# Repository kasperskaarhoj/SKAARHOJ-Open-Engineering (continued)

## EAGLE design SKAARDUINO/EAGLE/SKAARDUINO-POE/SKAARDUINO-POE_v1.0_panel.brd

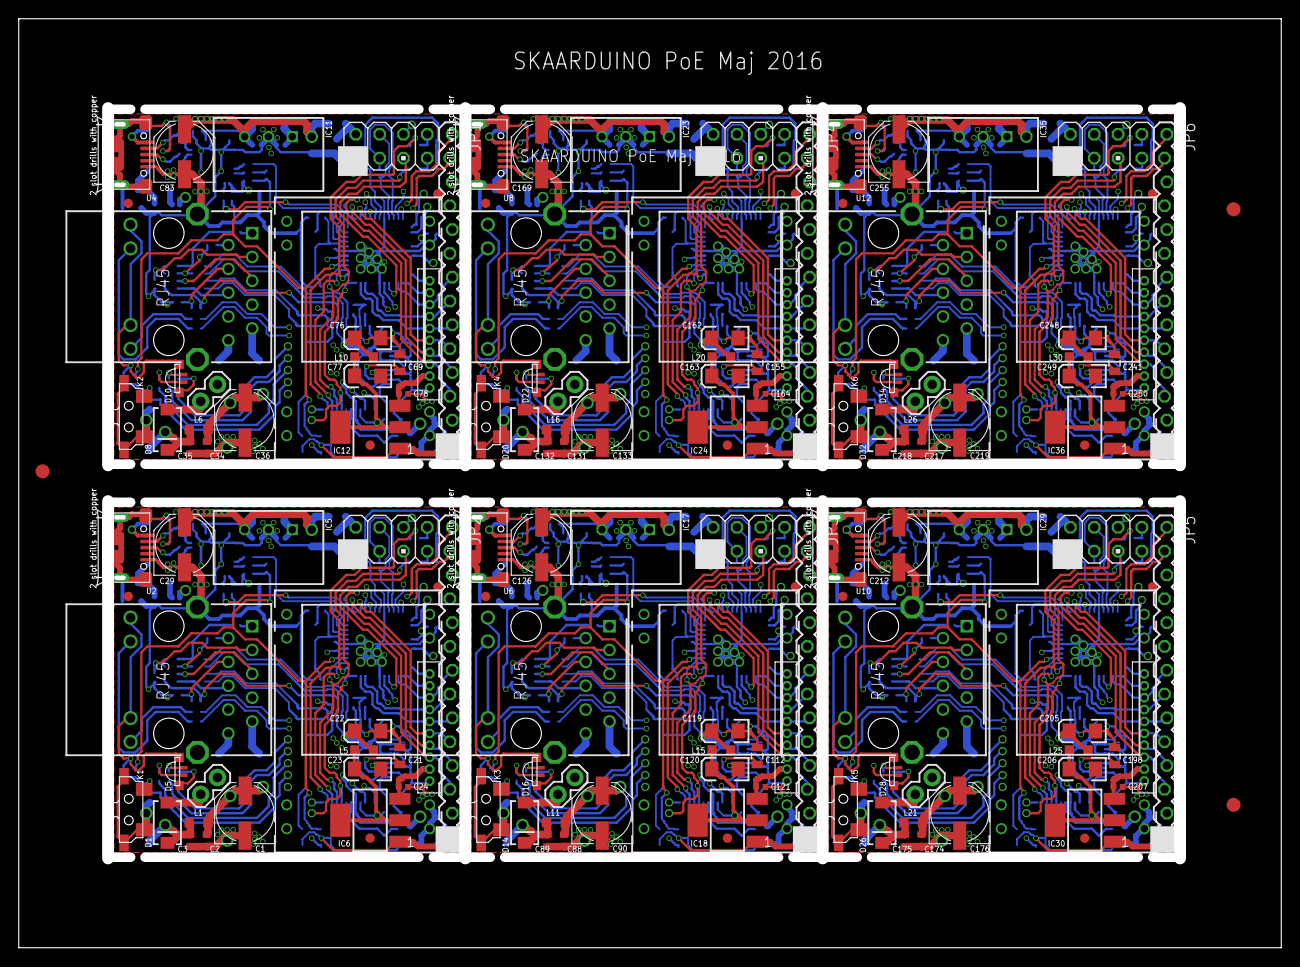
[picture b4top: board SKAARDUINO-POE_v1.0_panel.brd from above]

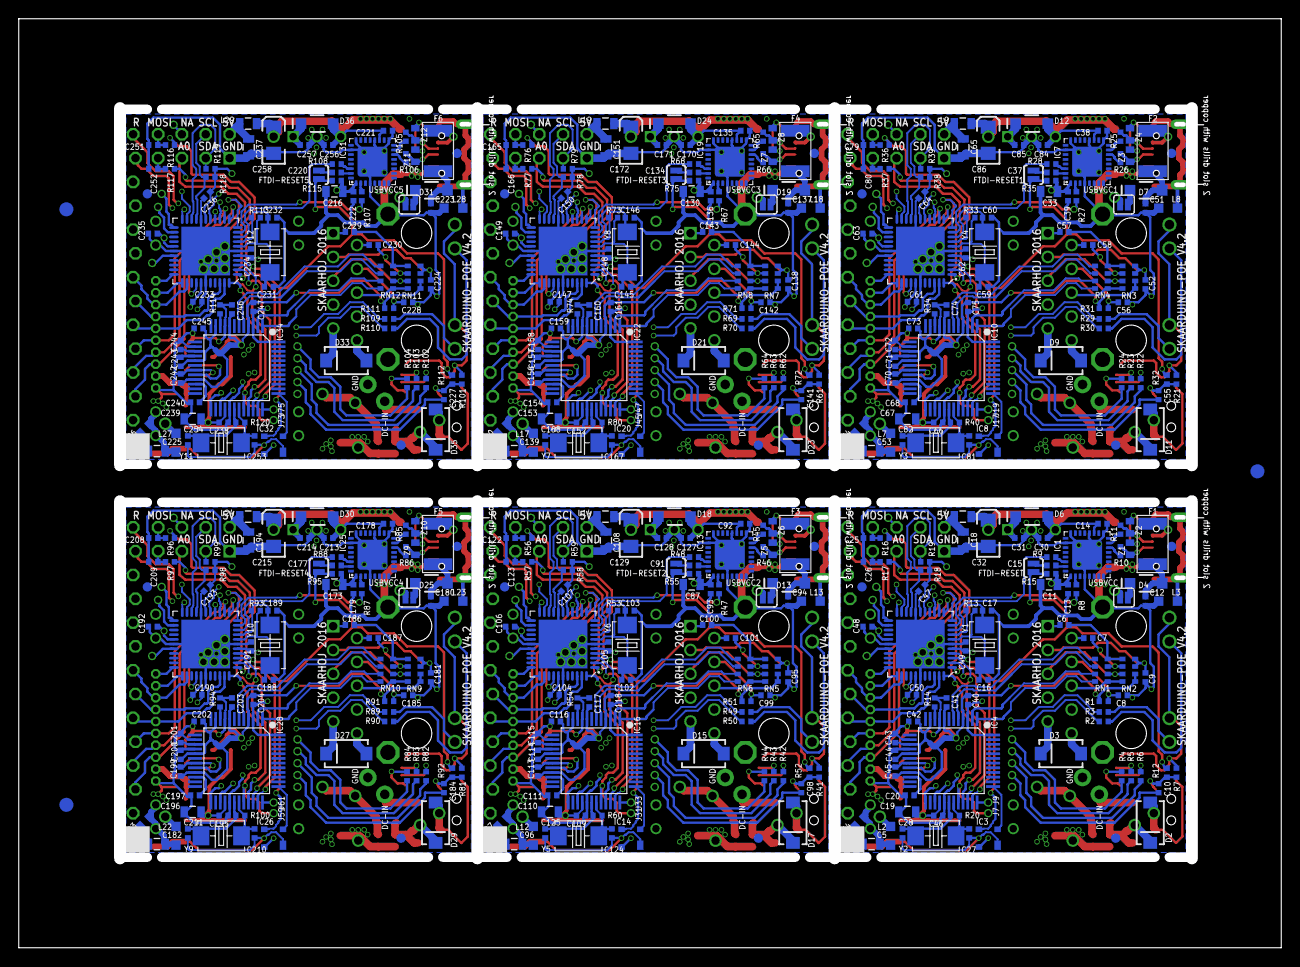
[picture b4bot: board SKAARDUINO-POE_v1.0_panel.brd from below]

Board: 4 copper layers, 134.6 x 99.1 mm, 690 parts (474 on the bottom side), 486 nets.

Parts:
C1, C36, C90, C133, C176, C219: 100uF/25V; PANASONIC_D
C2, C3, C4, C34, C35, C54, C88, C89, C97, C131, C132, C140, C174, C175, C183, C217, C218, C226: 100nF/25V; C0402
C5, C53, C96, C139, C182, C225: 10uF/25V; 0805
C6, C7, C57, C58, C100, C101, C143, C144, C186, C187, C229, C230: 6.8nF; 0402C
C8, C56, C99, C142, C185, C228: 22nF; 0402C
C9, C20, C52, C68, C95, C111, C138, C154, C181, C197, C224, C240: 10nF; 0402C
C10, C12, C51, C55, C94, C98, C137, C141, C180, C184, C223, C227: 1uF; 0402C
C11, C33, C87, C130, C173, C216: 22uF; 0805
C13, C14, C15, C24, C30, C37, C38, C39, C40, C41, C42, C43, C44, C45, C46, C47, C48, C49, C50, C61, C62, C63, C64, C66, C70, C71, C72, C73, C74, C75, C78, C84, C91, C92, C93, C104, C105, C106, C107, C109, C113, C114, C115, C116, C117, C118, C121, C127, C134, C135, C136, C147, C148, C149, C150, C152, C156, C157, C158, C159, C160, C161, C164, C170, C177, C178, C179, C190, C191, C192, C193, C195, C199, C200, C201, C202, C203, C204, C207, C213, C220, C221, C222, C233, C234, C235, C236, C238, C242, C243, C244, C245, C246, C247, C250, C256: 100nF; 0402C
C16, C17, C25, C26, C59, C60, C79, C80, C102, C103, C122, C123, C145, C146, C165, C166, C188, C189, C208, C209, C231, C232, C251, C252: 22pF; 0402C
C18, C65, C108, C151, C194, C237: 22uF/6.3V; 0805
C19, C67, C110, C153, C196, C239: 10uF/16V; 0805
C21, C69, C112, C155, C198, C241: 4.7uF; 0805
C22, C23, C32, C76, C77, C86, C119, C120, C129, C162, C163, C172, C205, C206, C215, C248, C249, C258: 10uF 6.3V A TANT; EIA3216
C27, C28, C81, C82, C124, C125, C167, C168, C210, C211, C253, C254: 18pF; 0402C
C29, C83, C126, C169, C212, C255: 330uF/6.3V; PANASONIC_D
C31, C85, C128, C171, C214, C257: 100nF/25V; 0402C
D1, D8, D14, D20, D26, D32: MBRA210LT3G; SMA-DIODE
D2, D3, D9, D11, D15, D17, D21, D23, D27, D29, D33, D35: SMAJ58CA; SMA-DIODE
D4, D6, D7, D12, D13, D18, D19, D24, D25, D30, D31, D36: MBR0520; SOD-123
D5, D10, D16, D22, D28, D34: KPFA-3010RGBC-11; LED-TRICOLOR-SMD
E$1, E$2, E$3: FIDUCIAL-1.5X3
E$4, E$5, E$6: FIDUCIAL-1.5X3_BOTTOM
F1, F2, F3, F4, F5, F6: SMD-PPTC-500MA-15V(1812); F1812
FID1, FID2, FID3, FID4, FID5, FID6, FID7, FID8, FID9, FID10, FID11, FID12, FID13, FID14, FID15, FID16, FID17, FID18, FID19, FID20, FID21, FID22, FID23, FID24, FID25, FID26, FID27, FID28, FID29, FID30, FID31, FID32, FID33, FID34, FID35, FID36: FIDUCIAL1X2.5; FIDUCIAL-1X2.5
FTDI-RESET, FTDI-RESET1, FTDI-RESET2, FTDI-RESET3, FTDI-RESET4, FTDI-RESET5: SOLDERJUMPERNO; SJ_2S-NO
IC1, IC7, IC13, IC19, IC25, IC31: FT232RQ; QFN32
IC2, IC9, IC15, IC21, IC27, IC33: ATMEGA1284P; QFN-44M1
IC3, IC8, IC14, IC20, IC26, IC32: APX811-44UG-7; SOT143-R
IC4, IC10, IC16, IC22, IC28, IC34: WizNet W5500; LQFP-48
IC5, IC11, IC17, IC23, IC29, IC35: RECOM 785.0-1.0; RECOM_785.0-1.0
IC6, IC12, IC18, IC24, IC30, IC36: LD1117S33CTR; SOT-223
J1, J3, J4, J6, J7, J13, J14, J17, J23, J24, J25, J26, J27, J28, J31, J37, J38, J39, J40, J41, J42, J45, J51, J52, J53, J54, J55, J56, J59, J65, J66, J67, J68, J69, J70, J73, J79, J80, J81, J82, J83, J84: SS; M1X1
J2, J15, J29, J43, J57, J71: DC IN JACK; 1X02
J5, J16, J30, J44, J58, J72: M04X2M2X4SMALLER; M2X4SMALLER
J8, J18, J32, J46, J60, J74: M10_1.27; M10X1
J9, J19, J33, J47, J61, J75: W_INT; M1X1
J10, J20, J34, J48, J62, J76: D11; M1X1
J11, J21, J35, J49, J63, J77: D12; M1X1
J12, J22, J36, J50, J64, J78: AREF; M1X1
JP1, JP2, JP3, JP4, JP5, JP6: M14LOCK; 1X14_LOCK
K1, K2, K3, K4, K5, K6: RESET/CFG; SW4-SMD-7.0X3.5X3.5MM-90D
L1, L2, L3, L6, L7, L8, L11, L12, L13, L16, L17, L18, L21, L22, L23, L26, L27, L28: Bead ILHB0805ER121V; L2012C
L4, L9, L14, L19, L24, L29: Bead ILHB0805ER121V; 0805
L5, L10, L15, L20, L25, L30: 1uH 250mA 0805; L2012C
R1, R31, R51, R71, R91, R111: 10R/1%; 0402
R2, R3, R29, R30, R49, R50, R69, R70, R89, R90, R109, R110: 470R; 0402
R4, R24, R44, R64, R84, R104: 390R; 0402
R5, R23, R43, R63, R83, R103: 540R; 0402
R6, R22, R42, R62, R82, R102: 2K7; 0402
R7, R15, R21, R35, R41, R55, R61, R75, R81, R95, R101, R115: 10K; 0402
R8, R9, R27, R28, R47, R48, R67, R68, R87, R88, R107, R108: 1K; 0402
R10, R11, R25, R26, R45, R46, R65, R66, R85, R86, R105, R106: 22R; 0402
R12, R32, R52, R72, R92, R112: 100K; 0402
R13, R20, R33, R40, R53, R60, R73, R80, R93, R100, R113, R120: 1M; 0402
R14, R34, R54, R74, R94, R114: 12K4 / 1%; 0402
R16, R17, R36, R37, R56, R57, R76, R77, R96, R97, R116, R117: 100R; 0402
R18, R19, R38, R39, R58, R59, R78, R79, R98, R99, R118, R119: 1K5; 0402
RN1, RN4, RN6, RN8, RN10, RN12: 33R; CAY16
RN2, RN3, RN5, RN7, RN9, RN11: 49R9 1%; CAY16
U1, U3, U5, U7, U9, U11: HY931147C-RJ45; HY931147C
U2, U4, U6, U8, U10, U12: MICRO USB; MICRO-USB5+4P-SMD-0.65-B
U$1, U$2, U$3, U$4, U$5, U$7: AG9800PTH
USBVCC, USBVCC1, USBVCC2, USBVCC3, USBVCC4, USBVCC5: SOLDERJUMPERNC; SJ_2S
Y1, Y4, Y6, Y8, Y10, Y12: 20MhZ; X2-SMD-5.0X3.2X1.3MM
Y2, Y3, Y5, Y7, Y9, Y11: 25MhZ; X2-SMD-5.0X3.2X1.3MM
Z1, Z2, Z3, Z4, Z5, Z6, Z7, Z8, Z9, Z10, Z11, Z12: PGB1010603; C0402

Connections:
3V3A: C22.A, C40.1, C41.1, C42.1, C43.1, C44.1, C45.1, IC4.4, IC4.8, IC4.11, IC4.15, IC4.17, IC4.21, L5.2, R1.2, RN2.5, RN2.6
3V3A1: C70.1, C71.1, C72.1, C73.1, C74.1, C75.1, C76.A, IC10.4, IC10.8, IC10.11, IC10.15, IC10.17, IC10.21, L10.2, R31.2, RN3.5, RN3.6
3V3A2: C113.1, C114.1, C115.1, C116.1, C117.1, C118.1, C119.A, IC16.4, IC16.8, IC16.11, IC16.15, IC16.17, IC16.21, L15.2, R51.2, RN5.5, RN5.6
3V3A3: C156.1, C157.1, C158.1, C159.1, C160.1, C161.1, C162.A, IC22.4, IC22.8, IC22.11, IC22.15, IC22.17, IC22.21, L20.2, R71.2, RN7.5, RN7.6
3V3A4: C199.1, C200.1, C201.1, C202.1, C203.1, C204.1, C205.A, IC28.4, IC28.8, IC28.11, IC28.15, IC28.17, IC28.21, L25.2, R91.2, RN9.5, RN9.6
3V3A5: C242.1, C243.1, C244.1, C245.1, C246.1, C247.1, C248.A, IC34.4, IC34.8, IC34.11, IC34.15, IC34.17, IC34.21, L30.2, R111.2, RN11.5, RN11.6
3V3D: C19.1, C23.A, C46.1, IC4.28, IC6.2, IC6.TER, L5.1
3V3D1: C66.1, C67.1, C77.A, IC10.28, IC12.2, IC12.TER, L10.1
3V3D2: C109.1, C110.1, C120.A, IC16.28, IC18.2, IC18.TER, L15.1
3V3D3: C152.1, C153.1, C163.A, IC22.28, IC24.2, IC24.TER, L20.1
3V3D4: C195.1, C196.1, C206.A, IC28.28, IC30.2, IC30.TER, L25.1
3V3D5: C238.1, C239.1, C249.A, IC34.28, IC36.2, IC36.TER, L30.1
5V: C11.1, C13.2, C14.2, C24.1, C29.+, C30.1, C32.A, C47.1, C48.1, C49.1, C50.1, D5.A, D6.2, IC1.1, IC1.19, IC2.5, IC2.17, IC2.27, IC2.38, IC3.4, IC5.P$3, IC6.3, J8.2, JP2.13, L4.2, R7.2, R15.2, R18.2, R19.2, U1.P$11, U1.P$13, USBVCC.2
5V1: C33.1, C38.2, C39.2, C61.1, C62.1, C63.1, C64.1, C78.1, C83.+, C84.1, C86.A, D10.A, D12.2, IC7.1, IC7.19, IC8.4, IC9.5, IC9.17, IC9.27, IC9.38, IC11.P$3, IC12.3, J18.2, JP1.13, L9.2, R21.2, R35.2, R38.2, R39.2, U3.P$11, U3.P$13, USBVCC1.2
5V2: C87.1, C92.2, C93.2, C104.1, C105.1, C106.1, C107.1, C121.1, C126.+, C127.1, C129.A, D16.A, D18.2, IC13.1, IC13.19, IC14.4, IC15.5, IC15.17, IC15.27, IC15.38, IC17.P$3, IC18.3, J32.2, JP3.13, L14.2, R41.2, R55.2, R58.2, R59.2, U5.P$11, U5.P$13, USBVCC2.2
5V3: C130.1, C135.2, C136.2, C147.1, C148.1, C149.1, C150.1, C164.1, C169.+, C170.1, C172.A, D22.A, D24.2, IC19.1, IC19.19, IC20.4, IC21.5, IC21.17, IC21.27, IC21.38, IC23.P$3, IC24.3, J46.2, JP4.13, L19.2, R61.2, R75.2, R78.2, R79.2, U7.P$11, U7.P$13, USBVCC3.2
5V4: C173.1, C178.2, C179.2, C190.1, C191.1, C192.1, C193.1, C207.1, C212.+, C213.1, C215.A, D28.A, D30.2, IC25.1, IC25.19, IC26.4, IC27.5, IC27.17, IC27.27, IC27.38, IC29.P$3, IC30.3, J60.2, JP5.13, L24.2, R81.2, R95.2, R98.2, R99.2, U9.P$11, U9.P$13, USBVCC4.2
5V5: C216.1, C221.2, C222.2, C233.1, C234.1, C235.1, C236.1, C250.1, C255.+, C256.1, C258.A, D34.A, D36.2, IC31.1, IC31.19, IC32.4, IC33.5, IC33.17, IC33.27, IC33.38, IC35.P$3, IC36.3, J74.2, JP6.13, L29.2, R101.2, R115.2, R118.2, R119.2, U11.P$11, U11.P$13, USBVCC5.2
A0: IC2.37, J5.5
A1: IC9.37, J16.5
A2: IC2.35, J8.8, JP2.7
A3: IC2.34, J8.9
A4: IC2.33, J8.10
A5: IC9.35, J18.8, JP1.7
A6: IC9.34, J18.9
A7: IC9.33, J18.10
A8: IC15.37, J30.5
A9: IC15.35, J32.8, JP3.7
A10: IC15.34, J32.9
A11: IC15.33, J32.10
A12: IC21.37, J44.5
A13: IC21.35, J46.8, JP4.7
A14: IC21.34, J46.9
A15: IC21.33, J46.10
A16: IC27.37, J58.5
A17: IC27.35, J60.8, JP5.7
A18: IC27.34, J60.9
A19: IC27.33, J60.10
A20: IC33.37, J72.5
A21: IC33.35, J74.8, JP6.7
A22: IC33.34, J74.9
A23: IC33.33, J74.10
ACTLED: IC4.27, R3.1
ACTLED1: IC10.27, R29.1
ACTLED2: IC16.27, R49.1
ACTLED3: IC22.27, R69.1
ACTLED4: IC28.27, R89.1
ACTLED5: IC34.27, R109.1
CFG: IC2.21, J4.1, R12.1
CFG1: IC9.21, J25.1, R32.1
CFG2: IC15.21, J39.1, R52.1
CFG3: IC21.21, J53.1, R72.1
CFG4: IC27.21, J67.1, R92.1
CFG5: IC33.21, J81.1, R112.1
CFGSW: C10.2, K1.1, R7.1, R12.2
CFGSW1: C55.2, K2.1, R21.1, R32.2
CFGSW2: C98.2, K3.1, R41.1, R52.2
CFGSW3: C141.2, K4.1, R61.1, R72.2
CFGSW4: C184.2, K5.1, R81.1, R92.2
CFGSW5: C227.2, K6.1, R101.1, R112.2
D0_RX: IC2.9, R9.2
D0_RX1: IC9.9, R28.2
D0_RX2: IC15.9, R48.2
D0_RX3: IC21.9, R68.2
D0_RX4: IC27.9, R88.2
D0_RX5: IC33.9, R108.2
D1: IC9.15, J23.1, R23.1
D1_TX: IC2.10, R8.2
D1_TX1: IC9.10, R27.2
D1_TX2: IC15.10, R47.2
D1_TX3: IC21.10, R67.2
D1_TX4: IC27.10, R87.2
D1_TX5: IC33.10, R107.2
D2: IC2.11, J8.3, JP2.12
D3: IC2.12, J8.4, JP2.11
D4: IC2.13, J8.5, JP2.10
D5: IC2.14, J13.1, R4.1
D6: IC2.15, J1.1, R5.1
D7: IC2.16, J3.1, R6.1
D8: IC2.42, J8.7, JP2.8
D9: IC2.43, J8.6, JP2.9
D10: IC2.22, J6.1
D10_SS: IC2.44, IC4.32, J7.1
D10_SS1: IC9.44, IC10.32, J17.1
D10_SS2: IC15.44, IC16.32, J31.1
D10_SS3: IC21.44, IC22.32, J45.1
D10_SS4: IC27.44, IC28.32, J59.1
D10_SS5: IC33.44, IC34.32, J73.1
D11: IC2.23, J10.1
D11_MOSI: IC2.1, IC4.35, R16.2
D11_MOSI1: IC9.1, IC10.35, R36.2
D11_MOSI2: IC15.1, IC16.35, R56.2
D11_MOSI3: IC21.1, IC22.35, R76.2
D11_MOSI4: IC27.1, IC28.35, R96.2
D11_MOSI5: IC33.1, IC34.35, R116.2
D12: IC2.24, J11.1
D12_MISO: IC2.2, IC4.34, JP2.2
D12_MISO1: IC9.2, IC10.34, JP1.2
D12_MISO2: IC15.2, IC16.34, JP3.2
D12_MISO3: IC21.2, IC22.34, JP4.2
D12_MISO4: IC27.2, IC28.34, JP5.2
D12_MISO5: IC33.2, IC34.34, JP6.2
D13: IC9.16, J24.1, R22.1
D13_SCK: IC2.3, IC4.33, R17.2
D13_SCK1: IC9.3, IC10.33, R37.2
D13_SCK2: IC15.3, IC16.33, R57.2
D13_SCK3: IC21.3, IC22.33, R77.2
D13_SCK4: IC27.3, IC28.33, R97.2
D13_SCK5: IC33.3, IC34.33, R117.2
D14: IC9.14, J27.1, R24.1
D15: IC9.22, J26.1
D16: IC9.11, J18.3, JP1.12
D17: IC9.12, J18.4, JP1.11
D18: IC9.13, J18.5, JP1.10
D19: IC9.43, J18.6, JP1.9
D20: IC9.42, J18.7, JP1.8
D21: IC9.23, J20.1
D22: IC9.24, J21.1
D23: IC15.15, J37.1, R43.1
D24: IC15.16, J38.1, R42.1
D25: IC15.14, J41.1, R44.1
D26: IC15.22, J40.1
D27: IC15.11, J32.3, JP3.12
D28: IC15.12, J32.4, JP3.11
D29: IC15.13, J32.5, JP3.10
D30: IC15.43, J32.6, JP3.9
D31: IC15.42, J32.7, JP3.8
D32: IC15.23, J34.1
D33: IC15.24, J35.1
D34: IC21.15, J51.1, R63.1
D35: IC21.16, J52.1, R62.1
D36: IC21.14, J55.1, R64.1
D37: IC21.22, J54.1
D38: IC21.11, J46.3, JP4.12
D39: IC21.12, J46.4, JP4.11
D40: IC21.13, J46.5, JP4.10
D41: IC21.43, J46.6, JP4.9
D42: IC21.42, J46.7, JP4.8
D43: IC21.23, J48.1
D44: IC21.24, J49.1
D45: IC27.15, J65.1, R83.1
D46: IC27.16, J66.1, R82.1
D47: IC27.14, J69.1, R84.1
D48: IC27.22, J68.1
D49: IC27.11, J60.3, JP5.12
D50: IC27.12, J60.4, JP5.11
D51: IC27.13, J60.5, JP5.10
D52: IC27.43, J60.6, JP5.9
D53: IC27.42, J60.7, JP5.8
D54: IC27.23, J62.1
D55: IC27.24, J63.1
D56: IC33.15, J79.1, R103.1
D57: IC33.16, J80.1, R102.1
D58: IC33.14, J83.1, R104.1
D59: IC33.22, J82.1
D60: IC33.11, J74.3, JP6.12
D61: IC33.12, J74.4, JP6.11
D62: IC33.13, J74.5, JP6.10
D63: IC33.43, J74.6, JP6.9
D64: IC33.42, J74.7, JP6.8
D65: IC33.23, J76.1
D66: IC33.24, J77.1
GND: C1.-, C2.2, C3.2, C4.2, C5.2, C8.1, C9.1, C11.2, C12.1, C13.1, C14.1, C16.1, C17.1, C18.1, C19.2, C20.2, C21.2, C22.C, C23.C, C24.2, C25.1, C26.1, C27.1, C28.1, C29.-, C30.2, C31.2, C32.C, C40.2, C41.2, C42.2, C43.2, C44.2, C45.2, C46.2, C47.2, C48.2, C49.2, C50.2, D2.A, IC1.4, IC1.17, IC1.20, IC1.24, IC1.26, IC2.6, IC2.18, IC2.28, IC2.39, IC2.TGND, IC3.1, IC4.3, IC4.9, IC4.14, IC4.16, IC4.19, IC4.29, IC4.48, IC5.P$2, IC6.1, J2.2, J5.1, J8.1, JP2.14, K1.2, K1.S1, K1.S2, L3.2, R14.1, U1.GND1, U1.GND2, U2.5, U$7.P3
GND1: C33.2, C34.2, C35.2, C36.-, C38.1, C39.1, C51.1, C52.1, C53.2, C54.2, C56.1, C59.1, C60.1, C61.2, C62.2, C63.2, C64.2, C65.1, C66.2, C67.2, C68.2, C69.2, C70.2, C71.2, C72.2, C73.2, C74.2, C75.2, C76.C, C77.C, C78.2, C79.1, C80.1, C81.1, C82.1, C83.-, C84.2, C85.2, C86.C, D11.A, IC7.4, IC7.17, IC7.20, IC7.24, IC7.26, IC8.1, IC9.6, IC9.18, IC9.28, IC9.39, IC9.TGND, IC10.3, IC10.9, IC10.14, IC10.16, IC10.19, IC10.29, IC10.48, IC11.P$2, IC12.1, J15.2, J16.1, J18.1, JP1.14, K2.2, K2.S1, K2.S2, L8.2, R34.1, U3.GND1, U3.GND2, U4.5, U$1.P3
GND2: C87.2, C88.2, C89.2, C90.-, C92.1, C93.1, C94.1, C95.1, C96.2, C97.2, C99.1, C102.1, C103.1, C104.2, C105.2, C106.2, C107.2, C108.1, C109.2, C110.2, C111.2, C112.2, C113.2, C114.2, C115.2, C116.2, C117.2, C118.2, C119.C, C120.C, C121.2, C122.1, C123.1, C124.1, C125.1, C126.-, C127.2, C128.2, C129.C, D17.A, IC13.4, IC13.17, IC13.20, IC13.24, IC13.26, IC14.1, IC15.6, IC15.18, IC15.28, IC15.39, IC15.TGND, IC16.3, IC16.9, IC16.14, IC16.16, IC16.19, IC16.29, IC16.48, IC17.P$2, IC18.1, J29.2, J30.1, J32.1, JP3.14, K3.2, K3.S1, K3.S2, L13.2, R54.1, U5.GND1, U5.GND2, U6.5, U$2.P3
GND3: C130.2, C131.2, C132.2, C133.-, C135.1, C136.1, C137.1, C138.1, C139.2, C140.2, C142.1, C145.1, C146.1, C147.2, C148.2, C149.2, C150.2, C151.1, C152.2, C153.2, C154.2, C155.2, C156.2, C157.2, C158.2, C159.2, C160.2, C161.2, C162.C, C163.C, C164.2, C165.1, C166.1, C167.1, C168.1, C169.-, C170.2, C171.2, C172.C, D23.A, IC19.4, IC19.17, IC19.20, IC19.24, IC19.26, IC20.1, IC21.6, IC21.18, IC21.28, IC21.39, IC21.TGND, IC22.3, IC22.9, IC22.14, IC22.16, IC22.19, IC22.29, IC22.48, IC23.P$2, IC24.1, J43.2, J44.1, J46.1, JP4.14, K4.2, K4.S1, K4.S2, L18.2, R74.1, U7.GND1, U7.GND2, U8.5, U$3.P3
GND4: C173.2, C174.2, C175.2, C176.-, C178.1, C179.1, C180.1, C181.1, C182.2, C183.2, C185.1, C188.1, C189.1, C190.2, C191.2, C192.2, C193.2, C194.1, C195.2, C196.2, C197.2, C198.2, C199.2, C200.2, C201.2, C202.2, C203.2, C204.2, C205.C, C206.C, C207.2, C208.1, C209.1, C210.1, C211.1, C212.-, C213.2, C214.2, C215.C, D29.A, IC25.4, IC25.17, IC25.20, IC25.24, IC25.26, IC26.1, IC27.6, IC27.18, IC27.28, IC27.39, IC27.TGND, IC28.3, IC28.9, IC28.14, IC28.16, IC28.19, IC28.29, IC28.48, IC29.P$2, IC30.1, J57.2, J58.1, J60.1, JP5.14, K5.2, K5.S1, K5.S2, L23.2, R94.1, U9.GND1, U9.GND2, U10.5, U$4.P3
GND5: C216.2, C217.2, C218.2, C219.-, C221.1, C222.1, C223.1, C224.1, C225.2, C226.2, C228.1, C231.1, C232.1, C233.2, C234.2, C235.2, C236.2, C237.1, C238.2, C239.2, C240.2, C241.2, C242.2, C243.2, C244.2, C245.2, C246.2, C247.2, C248.C, C249.C, C250.2, C251.1, C252.1, C253.1, C254.1, C255.-, C256.2, C257.2, C258.C, D35.A, IC31.4, IC31.17, IC31.20, IC31.24, IC31.26, IC32.1, IC33.6, IC33.18, IC33.28, IC33.39, IC33.TGND, IC34.3, IC34.9, IC34.14, IC34.16, IC34.19, IC34.29, IC34.48, IC35.P$2, IC36.1, J71.2, J72.1, J74.1, JP6.14, K6.2, K6.S1, K6.S2, L28.2, R114.1, U11.GND1, U11.GND2, U12.5, U$5.P3
I2C_SCL: IC2.19, J5.4, JP2.5, R18.1
I2C_SCL1: IC9.19, J16.4, JP1.5, R38.1
I2C_SCL2: IC15.19, J30.4, JP3.5, R58.1
I2C_SCL3: IC21.19, J44.4, JP4.5, R78.1
I2C_SCL4: IC27.19, J58.4, JP5.5, R98.1
I2C_SCL5: IC33.19, J72.4, JP6.5, R118.1
I2C_SDA: IC2.20, J5.3, JP2.6, R19.1
I2C_SDA1: IC9.20, J16.3, JP1.6, R39.1
I2C_SDA2: IC15.20, J30.3, JP3.6, R59.1
I2C_SDA3: IC21.20, J44.3, JP4.6, R79.1
I2C_SDA4: IC27.20, J58.3, JP5.6, R99.1
I2C_SDA5: IC33.20, J72.3, JP6.6, R119.1
LINKLED: IC4.25, R2.1
LINKLED1: IC10.25, R30.1
LINKLED2: IC16.25, R50.1
LINKLED3: IC22.25, R70.1
LINKLED4: IC28.25, R90.1
LINKLED5: IC34.25, R110.1
MOSI: C25.2, J5.8, JP2.3, R16.1
MOSI1: C79.2, J16.8, JP1.3, R36.1
MOSI2: C122.2, J30.8, JP3.3, R56.1
MOSI3: C165.2, J44.8, JP4.3, R76.1
MOSI4: C208.2, J58.8, JP5.3, R96.1
MOSI5: C251.2, J72.8, JP6.3, R116.1
unnamed: C8.2, R1.1, U1.P$4
unnamed: C15.2, FTDI-RESET.1
unnamed: D5.B, R6.2
unnamed: C3.1, D1.C, D2.C, L1.1
unnamed: D5.G, R5.2
unnamed: C12.2, D4.2, F1.2
unnamed: F1.1, U2.1
unnamed: C16.2, IC2.7, R13.2, Y1.2
unnamed: C7.2, U1.P$2
unnamed: J5.6, J14.1
unnamed: C6.2, U1.P$1
unnamed: C17.2, IC2.8, R13.1, Y1.1
unnamed: D1.A, J2.1
unnamed: C52.2, RN3.7, RN3.8, U3.P$3
unnamed: D5.R, R4.2
unnamed: R10.2, U2.3, Z1.1
unnamed: R11.2, U2.2, Z2.1
unnamed: C15.1, IC1.31
unnamed: C18.2, J5.2, L4.1
unnamed: C21.1, IC4.20
unnamed: L3.1, U2.S1, U2.S2, U2.S3, U2.S4, U2.S5, U2.S6, Z1.2, Z2.2
unnamed: C20.1, IC4.22
unnamed: IC4.10, R14.2
unnamed: IC4.36, J9.1
unnamed: IC2.29, J12.1
unnamed: R30.2, U3.P$12
unnamed: R29.2, U3.P$14
unnamed: R26.2, U4.3, Z3.1
unnamed: R25.2, U4.2, Z4.1
unnamed: L8.1, U4.S1, U4.S2, U4.S3, U4.S4, U4.S5, U4.S6, Z3.2, Z4.2
unnamed: C51.2, D7.2, F2.2
unnamed: F2.1, U4.1
unnamed: C35.1, D8.C, D11.C, L6.1
unnamed: D8.A, J15.1
unnamed: D10.R, R24.2
unnamed: C37.1, IC7.31
unnamed: C56.2, R31.1, U3.P$4
unnamed: C58.2, U3.P$2
unnamed: C57.2, U3.P$1
unnamed: C59.2, IC9.7, R33.2, Y4.2
unnamed: C60.2, IC9.8, R33.1, Y4.1
unnamed: C65.2, J16.2, L9.1
unnamed: C69.1, IC10.20
unnamed: C68.1, IC10.22
unnamed: IC10.10, R34.2
unnamed: IC10.36, J19.1
unnamed: IC9.29, J22.1
unnamed: C37.2, FTDI-RESET1.1
unnamed: D10.B, R22.2
unnamed: D10.G, R23.2
unnamed: J16.6, J28.1
unnamed: C95.2, RN5.7, RN5.8, U5.P$3
unnamed: R50.2, U5.P$12
unnamed: R49.2, U5.P$14
unnamed: R46.2, U6.3, Z5.1
unnamed: R45.2, U6.2, Z6.1
unnamed: L13.1, U6.S1, U6.S2, U6.S3, U6.S4, U6.S5, U6.S6, Z5.2, Z6.2
unnamed: C94.2, D13.2, F3.2
unnamed: F3.1, U6.1
unnamed: C89.1, D14.C, D17.C, L11.1
unnamed: D14.A, J29.1
unnamed: D16.R, R44.2
unnamed: C91.1, IC13.31
unnamed: C99.2, R51.1, U5.P$4
unnamed: C101.2, U5.P$2
unnamed: R3.2, U1.P$14
unnamed: C100.2, U5.P$1
unnamed: C102.2, IC15.7, R53.2, Y6.2
unnamed: C103.2, IC15.8, R53.1, Y6.1
unnamed: C108.2, J30.2, L14.1
unnamed: C112.1, IC16.20
unnamed: C111.1, IC16.22
unnamed: IC16.10, R54.2
unnamed: IC16.36, J33.1
unnamed: IC15.29, J36.1
unnamed: C91.2, FTDI-RESET2.1
unnamed: D16.B, R42.2
unnamed: D16.G, R43.2
unnamed: J30.6, J42.1
unnamed: C138.2, RN7.7, RN7.8, U7.P$3
unnamed: R70.2, U7.P$12
unnamed: R69.2, U7.P$14
unnamed: R66.2, U8.3, Z7.1
unnamed: R65.2, U8.2, Z8.1
unnamed: L18.1, U8.S1, U8.S2, U8.S3, U8.S4, U8.S5, U8.S6, Z7.2, Z8.2
unnamed: C137.2, D19.2, F4.2
unnamed: F4.1, U8.1
unnamed: C132.1, D20.C, D23.C, L16.1
unnamed: D20.A, J43.1
unnamed: D22.R, R64.2
unnamed: C134.1, IC19.31
unnamed: C142.2, R71.1, U7.P$4
unnamed: C144.2, U7.P$2
unnamed: C143.2, U7.P$1
unnamed: C145.2, IC21.7, R73.2, Y8.2
unnamed: C146.2, IC21.8, R73.1, Y8.1
unnamed: C151.2, J44.2, L19.1
unnamed: C155.1, IC22.20
unnamed: C154.1, IC22.22
unnamed: IC22.10, R74.2
unnamed: IC22.36, J47.1
unnamed: IC21.29, J50.1
unnamed: C134.2, FTDI-RESET3.1
unnamed: D22.B, R62.2
unnamed: D22.G, R63.2
unnamed: J44.6, J56.1
unnamed: C181.2, RN9.7, RN9.8, U9.P$3
unnamed: R90.2, U9.P$12
unnamed: R89.2, U9.P$14
unnamed: R86.2, U10.3, Z9.1
unnamed: R85.2, U10.2, Z10.1
unnamed: L23.1, U10.S1, U10.S2, U10.S3, U10.S4, U10.S5, U10.S6, Z9.2, Z10.2
unnamed: C180.2, D25.2, F5.2
unnamed: F5.1, U10.1
unnamed: C175.1, D26.C, D29.C, L21.1
unnamed: D26.A, J57.1
unnamed: D28.R, R84.2
unnamed: C177.1, IC25.31
unnamed: C185.2, R91.1, U9.P$4
unnamed: C187.2, U9.P$2
unnamed: C186.2, U9.P$1
unnamed: C188.2, IC27.7, R93.2, Y10.2
unnamed: C189.2, IC27.8, R93.1, Y10.1
unnamed: C194.2, J58.2, L24.1
unnamed: C198.1, IC28.20
unnamed: C197.1, IC28.22
unnamed: IC28.10, R94.2
unnamed: IC28.36, J61.1
unnamed: IC27.29, J64.1
unnamed: C177.2, FTDI-RESET4.1
unnamed: D28.B, R82.2
unnamed: D28.G, R83.2
unnamed: J58.6, J70.1
unnamed: C224.2, RN11.7, RN11.8, U11.P$3
unnamed: R110.2, U11.P$12
unnamed: R109.2, U11.P$14
unnamed: R106.2, U12.3, Z11.1
unnamed: R105.2, U12.2, Z12.1
unnamed: L28.1, U12.S1, U12.S2, U12.S3, U12.S4, U12.S5, U12.S6, Z11.2, Z12.2
unnamed: C223.2, D31.2, F6.2
unnamed: F6.1, U12.1
unnamed: C218.1, D32.C, D35.C, L26.1
unnamed: D32.A, J71.1
unnamed: D34.R, R104.2
unnamed: C220.1, IC31.31
unnamed: C228.2, R111.1, U11.P$4
unnamed: C230.2, U11.P$2
unnamed: C229.2, U11.P$1
unnamed: C231.2, IC33.7, R113.2, Y12.2
unnamed: C232.2, IC33.8, R113.1, Y12.1
unnamed: C237.2, J72.2, L29.1
unnamed: C241.1, IC34.20
unnamed: C240.1, IC34.22
unnamed: IC34.10, R114.2
unnamed: IC34.36, J75.1
unnamed: IC33.29, J78.1
unnamed: C220.2, FTDI-RESET5.1
unnamed: D34.B, R102.2
unnamed: D34.G, R103.2
unnamed: J72.6, J84.1
unnamed: C9.2, RN2.7, RN2.8, U1.P$3
unnamed: R2.2, U1.P$12
POE_DC_RETURN: C4.1, C5.1, L2.1, U$7.P1, U$7.P2
POE_DC_RETURN1: C53.1, C54.1, L7.1, U$1.P1, U$1.P2
POE_DC_RETURN2: C96.1, C97.1, L12.1, U$2.P1, U$2.P2
POE_DC_RETURN3: C139.1, C140.1, L17.1, U$3.P1, U$3.P2
POE_DC_RETURN4: C182.1, C183.1, L22.1, U$4.P1, U$4.P2
POE_DC_RETURN5: C225.1, C226.1, L27.1, U$5.P1, U$5.P2
POE_VIN+: D3.C, U1.P$9, U$7.P5, U$7.P6
POE_VIN+1: D9.C, U3.P$9, U$1.P5, U$1.P6
POE_VIN+2: D15.C, U5.P$9, U$2.P5, U$2.P6
POE_VIN+3: D21.C, U7.P$9, U$3.P5, U$3.P6
POE_VIN+4: D27.C, U9.P$9, U$4.P5, U$4.P6
POE_VIN+5: D33.C, U11.P$9, U$5.P5, U$5.P6
POE_VIN-: D3.A, U1.P$10, U$7.P7, U$7.P8
POE_VIN-1: D9.A, U3.P$10, U$1.P7, U$1.P8
POE_VIN-2: D15.A, U5.P$10, U$2.P7, U$2.P8
POE_VIN-3: D21.A, U7.P$10, U$3.P7, U$3.P8
POE_VIN-4: D27.A, U9.P$10, U$4.P7, U$4.P8
POE_VIN-5: D33.A, U11.P$10, U$5.P7, U$5.P8
RD+: IC1.14, R10.1
RD+1: IC7.14, R26.1
RD+2: IC13.14, R46.1
RD+3: IC19.14, R66.1
RD+4: IC25.14, R86.1
RD+5: IC31.14, R106.1
RD-: IC1.15, R11.1
RD-1: IC7.15, R25.1
RD-2: IC13.15, R45.1
RD-3: IC19.15, R65.1
RD-4: IC25.15, R85.1
RD-5: IC31.15, R105.1
RESET: C10.1, FTDI-RESET.2, IC2.4, IC3.3, JP2.1, R15.1
RESET1: C55.1, FTDI-RESET1.2, IC8.3, IC9.4, JP1.1, R35.1
RESET2: C98.1, FTDI-RESET2.2, IC14.3, IC15.4, JP3.1, R55.1
RESET3: C141.1, FTDI-RESET3.2, IC20.3, IC21.4, JP4.1, R75.1
RESET4: C184.1, FTDI-RESET4.2, IC26.3, IC27.4, JP5.1, R95.1
RESET5: C227.1, FTDI-RESET5.2, IC32.3, IC33.4, JP6.1, R115.1
RXIN: IC4.5, RN1.6
RXIN1: IC10.5, RN4.6
RXIN2: IC16.5, RN6.6
RXIN3: IC22.5, RN8.6
RXIN4: IC28.5, RN10.6
RXIN5: IC34.5, RN12.6
RXIN_E: C7.1, RN1.3, RN2.2
RXIN_E1: C58.1, RN3.2, RN4.3
RXIN_E2: C101.1, RN5.2, RN6.3
RXIN_E3: C144.1, RN7.2, RN8.3
RXIN_E4: C187.1, RN9.2, RN10.3
RXIN_E5: C230.1, RN11.2, RN12.3
RXIP: IC4.6, RN1.5
RXIP1: IC10.6, RN4.5
RXIP2: IC16.6, RN6.5
RXIP3: IC22.6, RN8.5
RXIP4: IC28.6, RN10.5
RXIP5: IC34.6, RN12.5
RXIP_E: C6.1, RN1.4, RN2.1
RXIP_E1: C57.1, RN3.1, RN4.4
RXIP_E2: C100.1, RN5.1, RN6.4
RXIP_E3: C143.1, RN7.1, RN8.4
RXIP_E4: C186.1, RN9.1, RN10.4
RXIP_E5: C229.1, RN11.1, RN12.4
SCLK: C26.2, J5.7, JP2.4, R17.1
SCLK1: C80.2, J16.7, JP1.4, R37.1
SCLK2: C123.2, J30.7, JP3.4, R57.1
SCLK3: C166.2, J44.7, JP4.4, R77.1
SCLK4: C209.2, J58.7, JP5.4, R97.1
SCLK5: C252.2, J72.7, JP6.4, R117.1
TXON: IC4.1, RN1.8
TXON1: IC10.1, RN4.8
TXON2: IC16.1, RN6.8
TXON3: IC22.1, RN8.8
TXON4: IC28.1, RN10.8
TXON5: IC34.1, RN12.8
TXON_E: RN1.1, RN2.4, U1.P$6
TXON_E1: RN3.4, RN4.1, U3.P$6
TXON_E2: RN5.4, RN6.1, U5.P$6
TXON_E3: RN7.4, RN8.1, U7.P$6
TXON_E4: RN9.4, RN10.1, U9.P$6
TXON_E5: RN11.4, RN12.1, U11.P$6
TXOP: IC4.2, RN1.7
TXOP1: IC10.2, RN4.7
TXOP2: IC16.2, RN6.7
TXOP3: IC22.2, RN8.7
TXOP4: IC28.2, RN10.7
TXOP5: IC34.2, RN12.7
TXOP_E: RN1.2, RN2.3, U1.P$5
TXOP_E1: RN3.3, RN4.2, U3.P$5
TXOP_E2: RN5.3, RN6.2, U5.P$5
TXOP_E3: RN7.3, RN8.2, U7.P$5
TXOP_E4: RN9.3, RN10.2, U9.P$5
TXOP_E5: RN11.3, RN12.2, U11.P$5
USBRXD: IC1.30, R9.1
USBRXD1: IC7.30, R28.1
USBRXD2: IC13.30, R48.1
USBRXD3: IC19.30, R68.1
USBRXD4: IC25.30, R88.1
USBRXD5: IC31.30, R108.1
USBTXD: IC1.2, R8.1
USBTXD1: IC7.2, R27.1
USBTXD2: IC13.2, R47.1
USBTXD3: IC19.2, R67.1
USBTXD4: IC25.2, R87.1
USBTXD5: IC31.2, R107.1
USBVCC: D4.1, USBVCC.1
USBVCC1: D7.1, USBVCC1.1
USBVCC2: D13.1, USBVCC2.1
USBVCC3: D19.1, USBVCC3.1
USBVCC4: D25.1, USBVCC4.1
USBVCC5: D31.1, USBVCC5.1
VIN: C1.+, C2.1, C31.1, D6.1, IC5.P$1, L1.2, L2.2
VIN1: C34.1, C36.+, C85.1, D12.1, IC11.P$1, L6.2, L7.2
VIN2: C88.1, C90.+, C128.1, D18.1, IC17.P$1, L11.2, L12.2
VIN3: C131.1, C133.+, C171.1, D24.1, IC23.P$1, L16.2, L17.2
VIN4: C174.1, C176.+, C214.1, D30.1, IC29.P$1, L21.2, L22.2
VIN5: C217.1, C219.+, C257.1, D36.1, IC35.P$1, L26.2, L27.2
WIZRST: IC3.2, IC4.37
WIZRST1: IC8.2, IC10.37
WIZRST2: IC14.2, IC16.37
WIZRST3: IC20.2, IC22.37
WIZRST4: IC26.2, IC28.37
WIZRST5: IC32.2, IC34.37
XTLN: C28.2, IC4.30, R20.2, Y2.2
XTLN1: C82.2, IC10.30, R40.2, Y3.2
XTLN2: C125.2, IC16.30, R60.2, Y5.2
XTLN3: C168.2, IC22.30, R80.2, Y7.2
XTLN4: C211.2, IC28.30, R100.2, Y9.2
XTLN5: C254.2, IC34.30, R120.2, Y11.2
XTLP: C27.2, IC4.31, R20.1, Y2.1
XTLP1: C81.2, IC10.31, R40.1, Y3.1
XTLP2: C124.2, IC16.31, R60.1, Y5.1
XTLP3: C167.2, IC22.31, R80.1, Y7.1
XTLP4: C210.2, IC28.31, R100.1, Y9.1
XTLP5: C253.2, IC34.31, R120.1, Y11.1
